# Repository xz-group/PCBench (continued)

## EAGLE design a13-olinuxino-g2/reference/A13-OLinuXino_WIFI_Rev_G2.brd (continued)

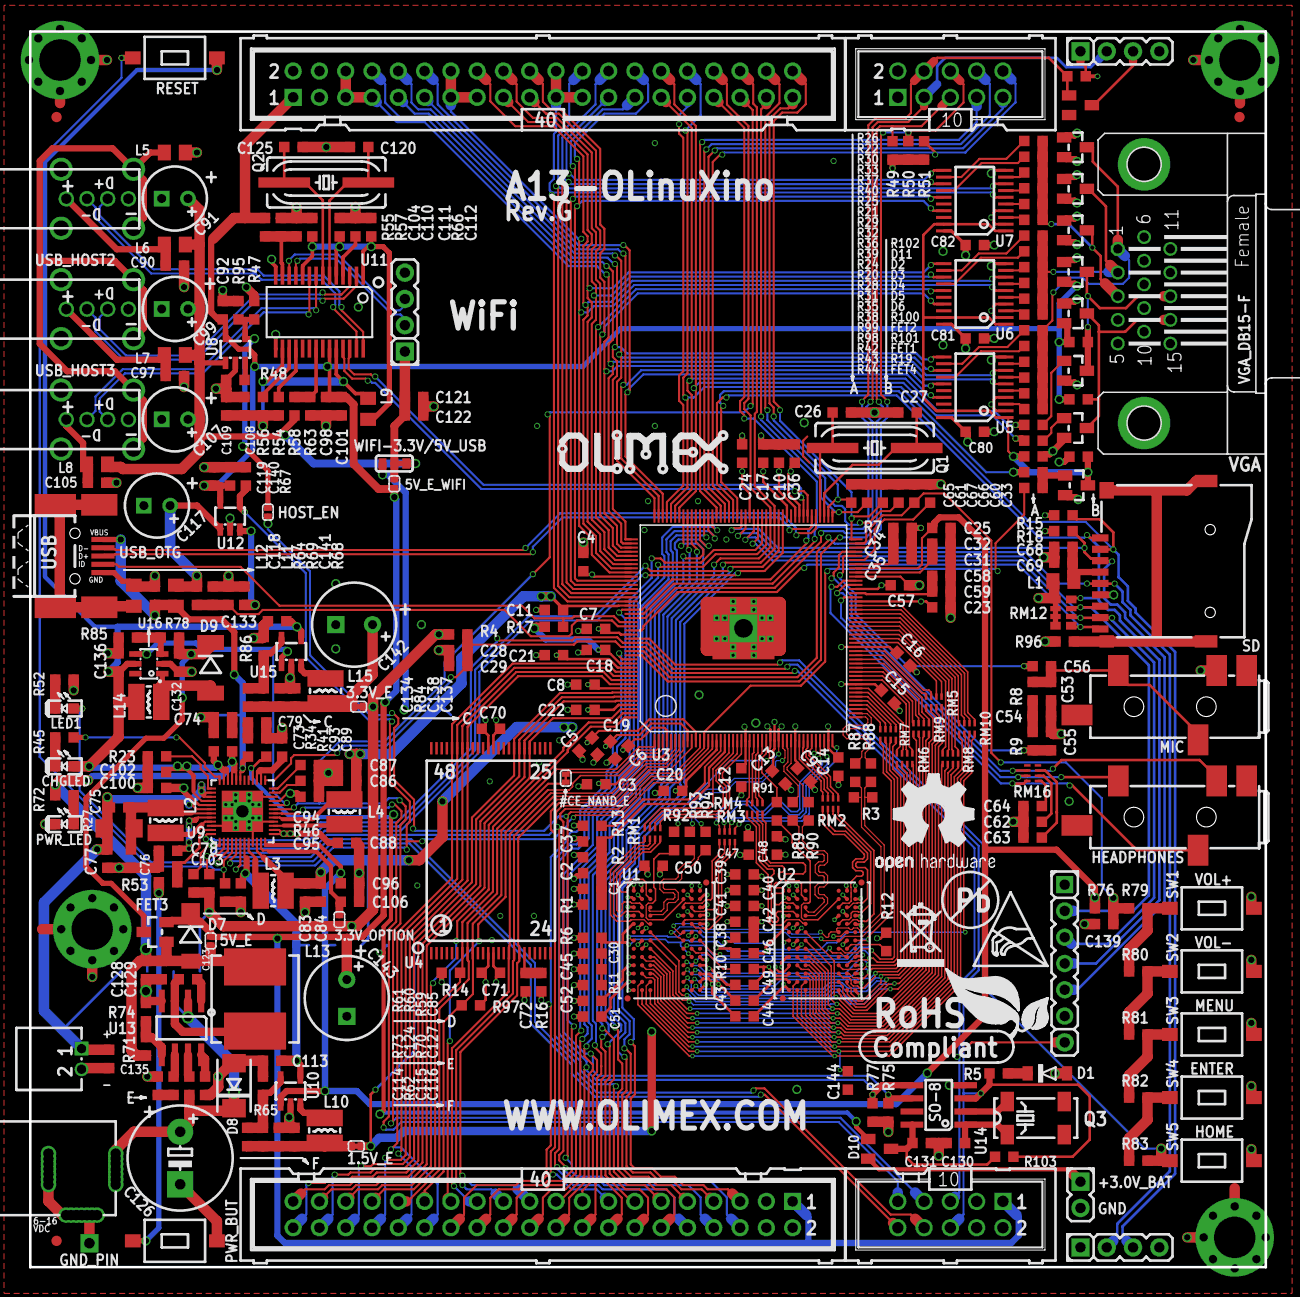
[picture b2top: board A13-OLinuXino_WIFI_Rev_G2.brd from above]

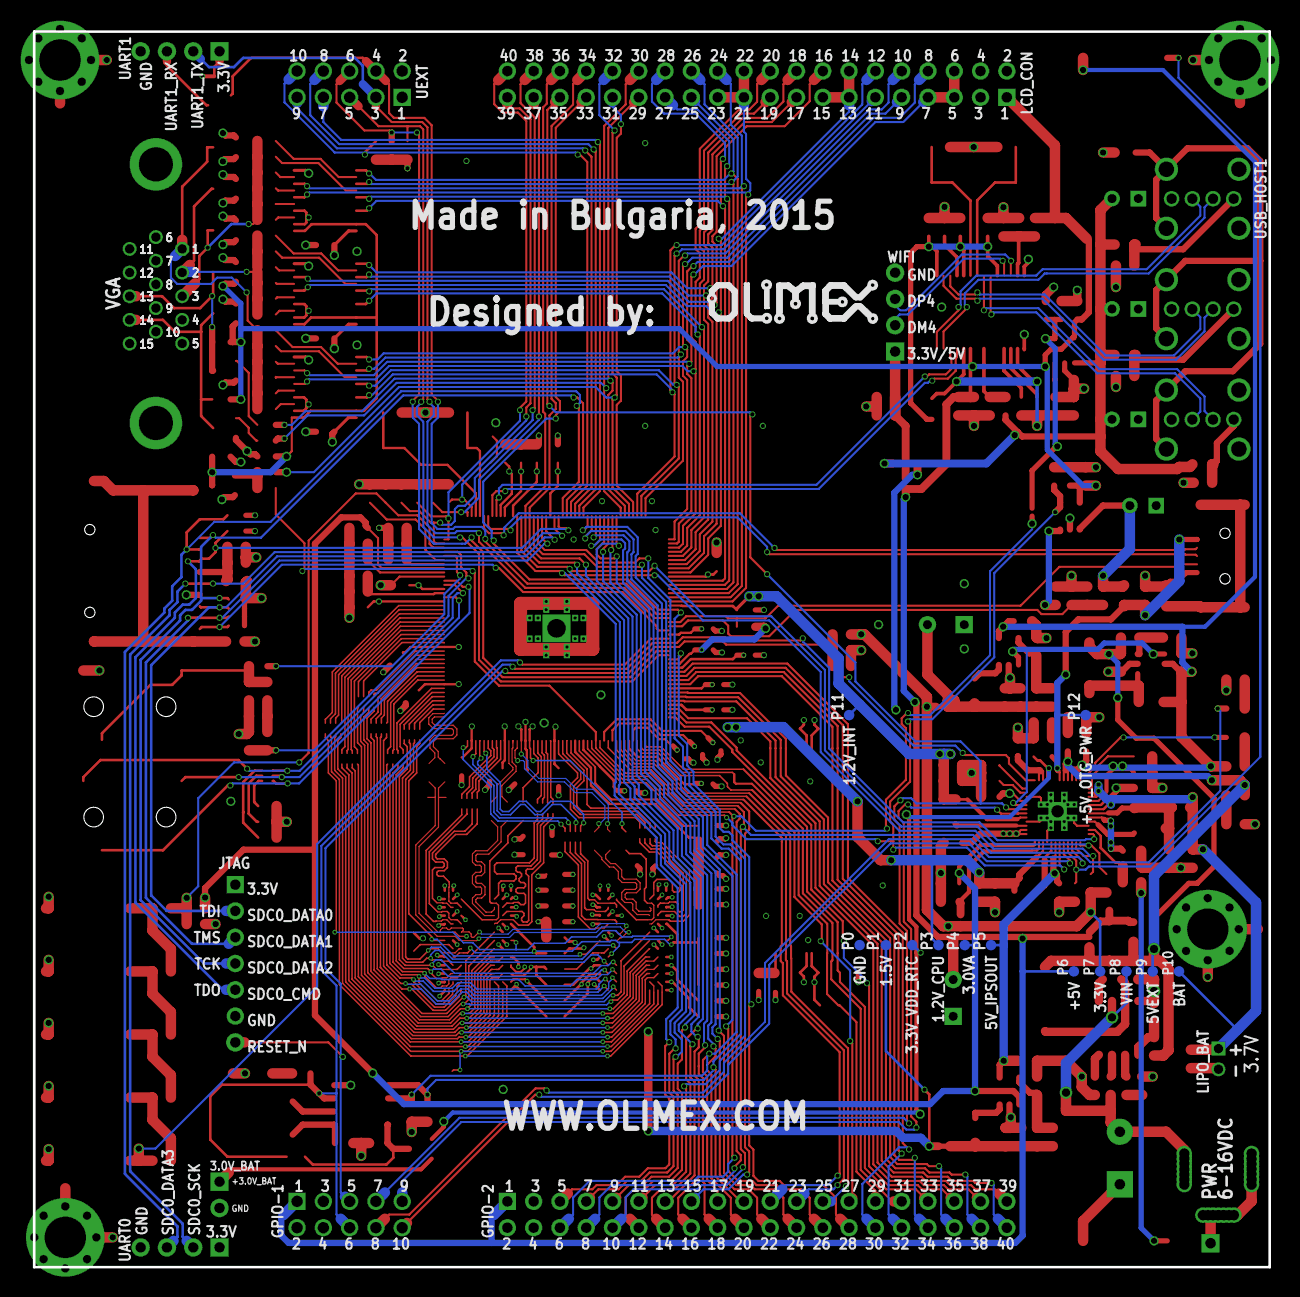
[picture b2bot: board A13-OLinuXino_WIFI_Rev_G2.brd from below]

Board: 4 copper layers, 119.4 x 119.4 mm, 371 parts (14 on the bottom side), 327 nets.

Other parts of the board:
U$5: LOGO-OPENHARDWARE_8X8
U$6, U$8: OLIMEX1_V
U$9: PB
U$10: ESD_SYMBOL
U$11: RECYCLE_BIN1/8
U$12: ROHS

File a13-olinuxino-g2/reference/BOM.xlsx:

Qty | Value | Device | Package | Parts | Description
1 | 0.03R/1% | R-EU_R1206_5MIL_WS | R1206_5MIL_WS | R27 | RESISTOR, European symbol
4 | 1.05k/1% | R-EU_R0603_5MIL_DWS | R0603_5MIL_DWS | R35, R36, R37, R74 | RESISTOR, European symbol
4 | 1.1k/1% | R-EU_R0603_5MIL_DWS | R0603_5MIL_DWS | R19, R85, R100, R101 | RESISTOR, European symbol
3 | 100k/1% | R-EU_R0603_5MIL_DWS | R0603_5MIL_DWS | R69, R76, R84 | RESISTOR, European symbol
57 | 100nF | C-EUC0603_DWS | C0603_DWS | C1, C2, C3, C4, C13, C15, C17, C19, C20, C21, C22, C23, C24, C29, C30, C32, C34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 | CAPACITOR, European symbol
1 | 100pF | C-EUC0603_DWS | C0603_DWS | C144 | CAPACITOR, European symbol
4 | 100uF/16V/LOWESR/105C/6.3x11mm_RM2.5 | CPOL-EUE2.5-6.3 | E2,5-6,3 | C91, C99, C107, C117 | POLARIZED CAPACITOR, European symbol
9 | 10k | R-EU_R0603_5MIL_DWS | R0603_5MIL_DWS | R14, R16, R18, R47, R55, R56, R96, R97, R103 | RESISTOR, European symbol
1 | 10k/1% | R-EU_R0603_5MIL_DWS | R0603_5MIL_DWS | R81 | RESISTOR, European symbol
1 | 10nF | C-EUC0603_DWS | C0603_DWS | C123 | CAPACITOR, European symbol
1 | 10pF | C-EUC0603_DWS | C0603_DWS | C130 | CAPACITOR, European symbol
31 | 10uF/6.3V | C-EUC0603_DWS | C0603_DWS | C6, C7, C8, C10, C11, C14, C16, C31, C35, C54, C55, C58, C73, C74, C76, C77, C7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 | CAPACITOR, European symbol
1 | 10uH/3.15A/20% | LLQH88PN100M38 | 8X8MM_3131 | L13
1 | 11k/1% | R-EU_R0603_5MIL_DWS | R0603_5MIL_DWS | R82 | RESISTOR, European symbol
2 | 13k/1% | R-EU_R0603_5MIL_DWS | R0603_5MIL_DWS | R68, R83 | RESISTOR, European symbol
3 | 17.8k/1% | R-EU_R0603_5MIL_DWS | R0603_5MIL_DWS | R20, R21, R22 | RESISTOR, European symbol
1 | 1N5819(S4SOD-123) | SCHOTKKY7.62SS-1N5819(S4SOD-123) | SOD-123 | D1
1 | 1N5822/SS34/SMA | D-MLL-41 | MELF-MLL41 | D9 | DIODE
1 | 1N5822/SS34/SMA | SCHOTKKY7.62SS2 | MLL-41 | D7
2 | 1R | R-EU_R0603_5MIL_DWS | R0603_5MIL_DWS | R34, R41 | RESISTOR, European symbol
9 | 1nF | C-EUC0603_DWS | C0603_DWS | C60, C61, C65, C66, C67, C84, C87, C103, C139 | CAPACITOR, European symbol
6 | 1uF | C-EUC0603_DWS | C0603_DWS | C28, C33, C75, C89, C94, C104 | CAPACITOR, European symbol
14 | 2.2k | R-EU_R0603_5MIL_DWS | R0603_5MIL_DWS | R8, R9, R45, R49, R50, R52, R53, R59, R60, R61, R72, R73, R75, R77 | RESISTOR, European symbol
3 | 2.2k/1% | R-EU_R0603_5MIL_DWS | R0603_5MIL_DWS | R31, R32, R33 | RESISTOR, European symbol
6 | 2.2uH/1.5A/DCR<0.1R/CD32 | L-CD32 | CD32 | L2, L3, L4, L10, L14, L15
3 | 200k/1% | R-EU_R0603_5MIL_DWS | R0603_5MIL_DWS | R7, R46, R67 | RESISTOR, European symbol
8 | 22R | R-EU_R0603_5MIL_DWS | R0603_5MIL_DWS | R87, R88, R89, R90, R91, R92, R93, R94 | RESISTOR, European symbol
1 | 22k/1% | R-EU_R0603_5MIL_DWS | R0603_5MIL_DWS | R86 | RESISTOR, European symbol
1 | 22pF | C-EUC0603_DWS | C0603_DWS | C114 | CAPACITOR, European symbol
1 | 22uF | C-EUC0603_DWS | C0603_DWS | C140 | CAPACITOR, European symbol
21 | 22uF/6.3V | C-EUC0603_DWS | C0603_DWS | C5, C9, C12, C18, C25, C42, C52, C68, C69, C71, C113, C115, C116, C128, C129, C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 | CAPACITOR, European symbol
4 | 240R/1% | R-EU_R0603_5MIL_DWS | R0603_5MIL_DWS | R10, R12, R13, R23 | RESISTOR, European symbol
4 | 2k/1% | R-EU_R0603_5MIL_DWS | R0603_5MIL_DWS | R1, R2, R6, R11 | RESISTOR, European symbol
1 | 3.3k/1% | R-EU_R0603_5MIL_DWS | R0603_5MIL_DWS | R65 | RESISTOR, European symbol
2 | 3.3nF | C-EUC0603_DWS | C0603_DWS | C53, C124 | CAPACITOR, European symbol
1 | 32768Hz/6pF | MC-306_32.768KHZ/SMD_8038 | MC-306 | Q3
4 | 33pF | C-EUC0603_DWS | C0603_DWS | C26, C27, C120, C125 | CAPACITOR, European symbol
4 | 4.32k/1% | R-EU_R0603_5MIL_DWS | R0603_5MIL_DWS | R28, R29, R30, R102 | RESISTOR, European symbol
2 | 4.99k/1% | R-EU_R0603_5MIL_DWS | R0603_5MIL_DWS | R62, R71 | RESISTOR, European symbol
1 | 470uF/25V/LOWESR/105C | CPOL-EUE5-10.5 | E5-10,5 | C126 | POLARIZED CAPACITOR, European symbol
7 | 47k | R-EU_R0603_5MIL_DWS | R0603_5MIL_DWS | R4, R5, R17, R51, R54, R64, R70 | RESISTOR, European symbol
1 | 47pF | C-EUC0603_DWS | C0603_DWS | C134 | CAPACITOR, European symbol
3 | 51R | R-EU_R0603_5MIL_DWS | R0603_5MIL_DWS | R43, R98, R99 | RESISTOR, European symbol
3 | 549R/1% | R-EU_R0603_5MIL_DWS | R0603_5MIL_DWS | R38, R39, R40 | RESISTOR, European symbol
2 | 6.8k/1% | R-EU_R0603_5MIL_DWS | R0603_5MIL_DWS | R48, R79 | RESISTOR, European symbol
1 | 680R/1% | R-EU_R0603_5MIL_DWS | R0603_5MIL_DWS | R66 | RESISTOR, European symbol
2 | 8.2k/1% | R-EU_R0603_5MIL_DWS | R0603_5MIL_DWS | R78, R80 | RESISTOR, European symbol
3 | 8.66k/1% | R-EU_R0603_5MIL_DWS | R0603_5MIL_DWS | R24, R25, R26 | RESISTOR, European symbol
1 | A13 | Allwinner A13 | TQFP176 | U3
1 | AXP209(QFN48) | AXP209 | QFN48 | U9
2 | BAT54C | DIODE_AC-CA_ | SOT23C | D10, D11 | DUAL DIODE
5 | BAT54S | DIODE_AC-AC_ | SOT23C(BAT54S) | D2, D3, D4, D5, D6 | DUAL DIODE
2 | BH10S | ML10 | ML10-MALE | GPIO-1, UEXT | HARTING
3 | BSS138 | N-MOS+DIODBSS138(SOT23-3) | SOT23 | FET1, FET2, FET4
1 | CL470nH/0805/1.76R/250mA | L-USL0805_5MIL_DWS | L0805_5MIL_DWS | L1 | INDUCTOR, American symbol
1 | DW02R | CON2DW02R | DW02R | LIPO_BAT
1 | FB0805/600R/200mA(201209-601) | L-USL0805_5MIL_DWS | L0805_5MIL_DWS | L12 | INDUCTOR, American symbol
6 | FB0805/600R/2A | L-USL0805_5MIL_DWS | L0805_5MIL_DWS | L5, L6, L7, L8, L9, L11 | INDUCTOR, American symbol
1 | GL850G-HHGXX | GL850G | SSOP28 | U11
2 | HC49/S1 | HC49/S1 | HC49/SMD2_THIN | Q1, Q2 | CRYSTAL
1 | IRLML6402 | P-MOS+DIODIRLML6402 | SOT23 | FET3
2 | K4B2G0846Q-BCKO | H5TQ2G83CFR-H9C | FBGA78 | U1, U2
1 | LED/GREEN/0603 | LED0603DWS | LED-0603 | LED1
1 | LED/RED/0603 | LED0603DWS | LED-0603 | PWR_LED
1 | LED/YELLOW/0603 | LED0603DWS | LED-0603 | CHGLED
1 | MICRO_SD/MMC_CP_NEWTFC-WPAPR-08 | MICRO_SD/MMC_CP_NEWTFC-WPAPR-08 | TFC-WPAPR-08 | SD
2 | 2.54 Pinhead 2x20 | 2.54 Pinhead 2x20 | 2.54 Pinhead 2x20 | GPIO-2, LCD_CON | HARTING
1 | MP1482DS | MP1482 | SOIC8 | U13
1 | PCF8563T/5 | PCF8563 | SO-8 | U14 | Real-time clock/calendar
2 | PJ-W47S-05D2-LF_V2 | AUDIO_JACK_5PINPJ-W47S-05D2-LF_V2 | PJ-W47S-05D2-LF_5PIN_V2 | HEADPHONES, MIC
11 | RA0805_(4X0402)_22R | R_MATRIX_4E_25X625 | R_MATRIX_4_0402_25X625 | RM1, RM2, RM3, RM4, RM5, RM6, RM7, RM8, RM9, RM10, RM16
1 | RA1206_(4X0603)_4B8_100K | R_MATRIX_4E | R_MATRIX_4 | RM12
1 | SMBJ16A | SMBJ16A | DO214AA | D8
3 | SN74ALVC244 | 74ALVC244 | PW | U5, U6, U7
2 | SY6280 | SY6280 | SOT23-5 | U8, U12
1 | SY7208(SOT23-6) | SY7208 | SOT23-6 | U16
2 | SY8008C(AA)C | SY8008 | SOT23-5 | U10, U15
7 | T1107A(6x3.8x2.5mm) | SW-TAKT6 | SW-TAKT_6X3.5_SMD | PWR_BUT, RESET, SW1, SW2, SW3, SW4, SW5
1 | USB-OTG | MINI_USB9 | USB_MINI_9PIN | USB_OTG
3 | USB_A_VERTICAL | USB_SHIELDUSB_A_VERTICAL | USB_A_VERTICAL_PTH | USB_HOST1, USB_HOST2, USB_HOST3
1 | VGA15 | DB1522 | DB15-F_22MM | VGA_DB15-F
1 | YDJ-1136 | PWR-JAKPWR_JACK_UNI_MILLING | PWR_JACK_UNI_MILLING | PWR

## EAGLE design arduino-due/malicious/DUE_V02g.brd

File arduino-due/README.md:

# Getting Started with the Arduino-Due Benchmark

## Introduction
This tutorial includes step-by-step information about how to get started with the `arduino-due` benchmark, including both setting up the boards and demonstrating the attacks.

For this benchmark, there are two versions of boards (as shown below): the  `malicious` version and the `reference` version. The `reference` version uses the exact same schematic design of the original [Arduino Due board](https://store.arduino.cc/usa/due). 
Note that we slightly modify the layout of the original design to ease inserting the Trojans and implementing the attacks. The `malicious` version is the same as the `reference` version (both schematic and layout) except the inserted malicious circuit, which means once the malicious circuits and related routings are removed, the `malicious` version board will be completely the same as the `reference` version board.

In this benchmark we implement three malicious attacks (as shown above):
1. A malicious MOSFET is connected to the UART transmitter to leak information through LED (subfigure c);
2. The maliciously programmed ATtiny microcontroller monitors the UART and generates Flash erase signal when triggered (subfigure d); 
3. Two XOR logic chips output a signal to reset the board once triggered (subfigure e).

## Initialize the boards
### Install the firmware of the Arduino Due programming port
#### Use the Atmel programmer to install the firmware:
1. Follow the instruction of https://www.arduino.cc/en/Hacking/DFUProgramming8U2

2. For the firmware files, the `hex` files can be found in
https://github.com/arduino/ArduinoCore-sam/tree/master/firmwares/atmega16u2

3. After programming the flash, you will see the programming port of the Arduino Due board in your Device manager.

### Test the functionality of the boards
1. Install the Arduino SAM Boards (32-bits ARM Cortex M3) from the tools->board->boards manager.
#### Program through the Programming Port
1. Connect the Programming Port.
2. Upload and Run the `Blink` example.

#### Program through the Native USB Port

1. Connect the native USB port.
2. Program directly using the native USB port, upload and Run the `Blink` example.

## Demonstrate the attacks
### 1. Malicious MOSFET
**Goal:**<br> A malicious MOSFET is connected to the UART transmit pin to leak information through LED.

**Configuration:**<br> In this demonstration, the datapath is as follows:
User input into the reference board's Serial Monitor is sent directly to the Serial1 port on the victim board. This Serial1 port (on the victim board) is directly connected to the LED that is used to leak the data. Once the victim board receives data from the reference board, it mirrors the characters back over the same Serial1 port to be leaked through the LED. The data is also mirrored to the SerialUSB port which will display on the victim board's Serial Monitor if connected.

**Demonstration:**<br>

1. Connect Pins

| Reference Board | <------------> | Victim Board |
| ----------- | ----------- | ----------- |
| Serial1 TX (18) | <------------> | Serial1 RX (19) |
| Serial1 RX (19) | <------------> | Serial1 TX (18) |
| GND | <------------> | GND |

2. Upload Source Code

* Attach the victim board via USB and upload the following [source code](attacks/malicious_MOSFET/victim_board_src/victim_board_src.ino)
* Attach the reference board via USB and upload the following [source code](attacks/malicious_MOSFET/reference_board_src/reference_board_src.ino)

3. Testing

* Connect the reference board via USB
* Open the Serial Monitor (this is accessed by clicking the plus button in the top right corner on the Arduino IDE)
* Click the hardware reset button (located next to the USB port) on the reference board
* Wait 5 seconds for the board to initialize until you see an information printout
* Try entering various characters into the Serial Monitor
* Take note of the LED blinking on the victim board whenever characters are sent via the reference board
* To confirm that characters are being sent, connect the reference board via USB and open another Serial Monitor to track the mirrored characters being sent from the reference board

**Vulnerability:**<br> The flashing of the LED corresponds to the 1's and 0's of the ASCII being transmitted through UART. This data could be sensed and decoded by another system to monitor sensitive UART data packets.

### 2. Malicious ATtiny
**Goal:**<br> A maliciously programmed ATtiny microcontroller monitors the UART and generates a Flash erase signal when triggered.

**Generalized Configuration:**<br> In this demonstration, the datapath is as follows:
User input into the reference board's Serial Monitor is sent directly to the Serial2 port on the victim board. This Serial2 port (on the victim board) is directly monitored by the malicious ATtiny. Once the trigger word is inputted by the user and subsequently read by the ATtiny, the ATtiny triggers a master reset of the victim board's flash memory. Throughout this process, the victim board's LED will continuously blink to show that it is still functional and has not yet been attacked. Once it is attacked, the LED will stop blinking and the board will have to be re-flashed before it can perform another test.

**Technical Configuration:**<br>
* The ATtiny102 constantly monitors the victim board's UART RX pin at 4800 baud
    * This connection configuration is undetectable by the victim board itself or any reference boards
* A reference board is used to connect to the Serial 2 UART Port of the victim board (TX-16 RX-17)
    * The reference board can trigger the ATtiny102 to erase the flash of the victim board by sending the command "ATTACK"
* A 6-character buffer array is maintined on the ATtiny102 to keep track of incoming UART characters
    * Each time a new character is read, it is placed at the end of the array
    * Subsequently, all remaining characters are shifted one index to the left in the array
    * This process discards the oldest (leftmost) character
* Once the buffer array contains the string "ATTACK" the ERASE sequence is triggered:
    * The ATtiny102 pulls the ERASE pin of the victim board LOW for 2 seconds to erase the FLASH
    * At this point, the victim board is in a paralyzed state and the ATtiny102 resumes normal listening operation

**Demonstration:**
1. Connect Pins

| Reference Board | <------------> | Victim Board |
| ----------- | ----------- | ----------- |
| Serial2 TX (16) | <------------> | Serial1 RX (17) |
| Serial1 RX (17) | <------------> | Serial1 TX (16) |
| GND | <------------> | GND |

2. Upload Source Code

* Attach the victim board via USB and upload the following [source code](attacks/malicious_ATtiny/victim_board_src/victim_board_src.ino)
* Attach the reference board via USB and upload the following [source code](attacks/malicious_ATtiny/reference_board_src/reference_board_src.ino)
* If the ATtiny needs to be flashed, use Atmel/Microchip Studio to upload the following [source code](attacks/malicious_ATtiny/ATtiny_src)

3. Testing

* Connect the reference board via USB
* Open the Serial Monitor (this is accessed by clicking the plus button in the top right corner on the Arduino IDE)
* Click the hardware reset button (located next to the USB port) on the reference board
* Wait 5 seconds for the board to initialize until you see an information printout
* Try entering various characters (not the trigger word) into the Serial Monitor
* Take note of the LED blinking on the victim board which signifies that it has not yet been attacked
* Enter the trigger word into the Serial Monitor
* Confirm that the attack was successful be ensuring that the victim board's LED stopped blinking

**Vulnerability:**<br> The ATtiny can erase the Flash of the victim board, rendering it useless, if the trigger command is sent to the victim board over UART.

### 3. Malicious XORs
**Goal:**<br> Two XOR logic chips output a signal to reset the victim board's Flash once triggered.

**Generalized Configuration:**<br> In this demonstration, the datapath is as follows:
User input into the reference board's Serial Monitor is monitored internally by the reference board. Once the trigger word is inputted by the user, a sequence of code executes that triggers a flash reset on the victim board. This is accomplished by setting pins 44, 45, and 46 on the victim board to a specific sequence of logic levels that trigger the flash reset. Throughout this process, the victim board's LED will continuously blink to show that it is still functional and has not yet been attacked. Once it is attacked, the LED will stop blinking and the board will have to be re-flashed before it can perform another test.

**Technical Configuration:**<br>
* The XOR chips have pins 44, 45, 46 from the victim board as inputs. In the default state, these pins are logical level HIGH so as to not trigger the Flash reset.
* The following truth table represents the various logic level inputs to the victim board and what output they trigger

| Pin 44      | Pin 45      | Pin 46      | Flash Reset |
| ----------- | ----------- | ----------- | -----------  |
|0|0|0|NO|
|0|0|1|<mark>YES<mark>|
|0|1|0|<mark>YES<mark>|
|0|1|1|NO|
|1|0|0|<mark>YES<mark>|
|1|0|1|NO|
|1|1|0|NO|
|1|1|1|<mark>YES<mark>|

**Demonstration:**
1. Connect Pins

| Reference Board | <------------> | Victim Board |
| ----------- | ----------- | ----------- |
| D10 | <------------> | D44 |
| D11 | <------------> | D45 |
| D12 | <------------> | D46 |
| GND | <------------> | GND |

2. Upload Source Code

* Attach the victim board via USB and upload the following [source code](attacks/malicious_ATtiny/victim_board_src/victim_board_src.ino)
* Attach the reference board via USB and upload the following [source code](attacks/malicious_ATtiny/reference_board_src/reference_board_src.ino)

3. Testing

* Connect the reference board via USB
* Open the Serial Monitor (this is accessed by clicking the plus button in the top right corner on the Arduino IDE)
* Click the hardware reset button (located next to the USB port) on the reference board
* Wait 5 seconds for the board to initialize until you see an information printout
* Try entering various characters (not the trigger word) into the Serial Monitor
* Take note of the LED blinking on the victim board which signifies that it has not yet been attacked
* Enter the trigger word into the Serial Monitor
* Confirm that the attack was successful be ensuring that the victim board's LED stopped blinking

**Vulnerability:**<br> An external board can change the state of these input pins which would trigger a Flash reset of the victim board, rendering is useless.

## Developer Notes
* For an 8MHz internal clock on the ATtiny102, the prescaler sets the clock in the code to 1MHz
    * 1 MHz is not considered fast enough to communicated over UART at 9600 baud becuase data becomes corrupted
    * 4800 is the maximum clean baud rate for this internal clock
* ATtiny102 TX trace should be removed in final design
* Use other, non-programming pin, for the resetting functionality on the ATtiny102 (recommend PB1/Pin 5)
* The programming port on the test boards does not work due to a an error in the original Arduino Due design documentation

## References
1. Pinout of the Arduino Due Board: https://content.arduino.cc/assets/Pinout-Due_latest.pdf

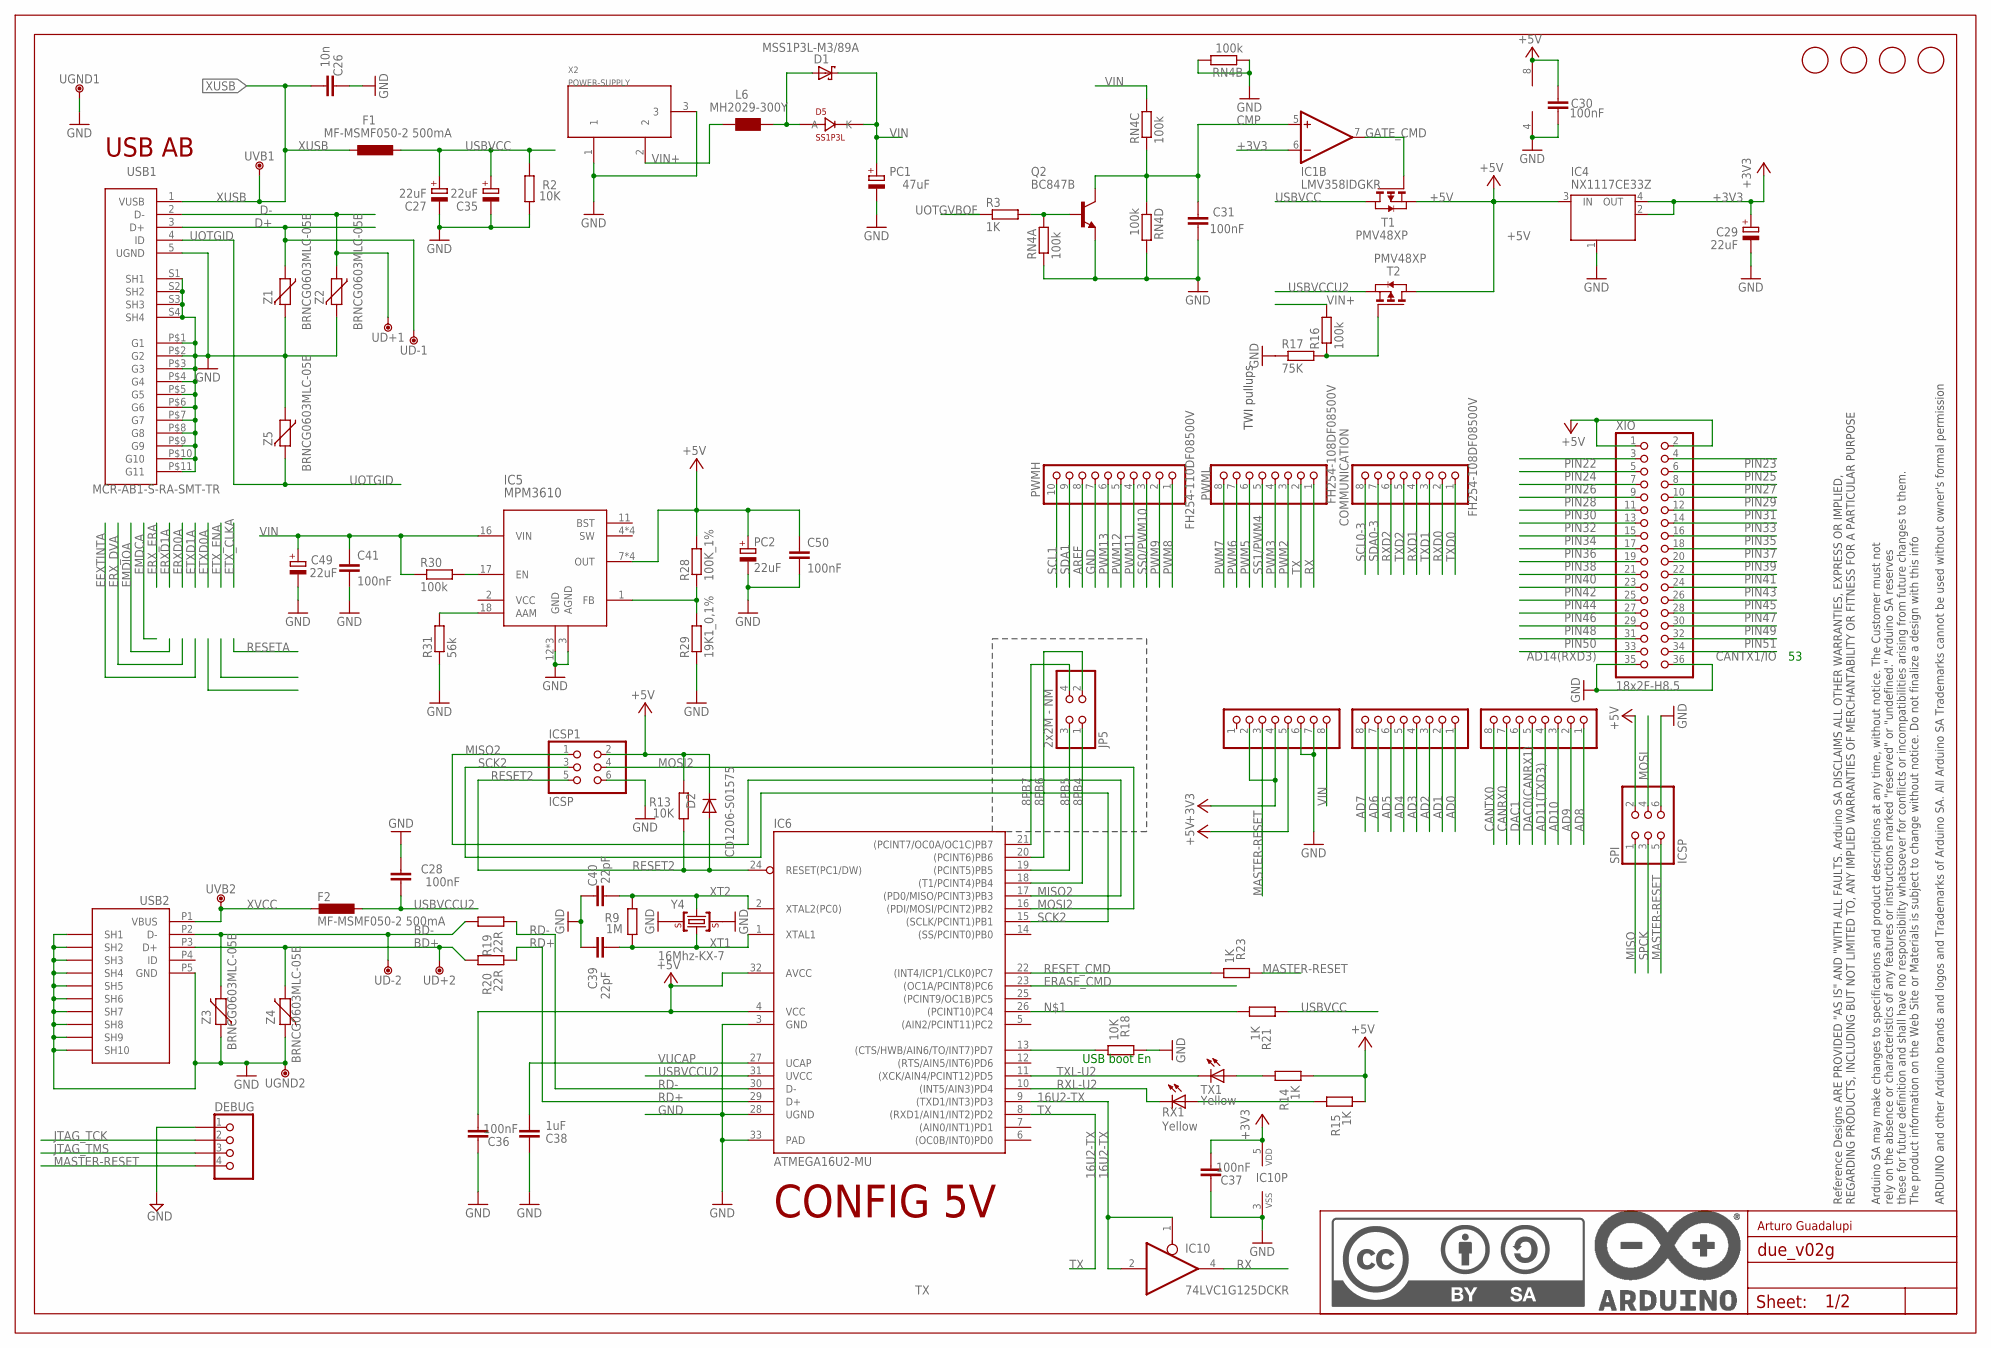
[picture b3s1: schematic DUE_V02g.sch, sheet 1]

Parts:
ADCH: FH254-108DF08500V; 1X08
ADCL: FH254-108DF08500V; 1X08
C26: 10n; C0402
C27, C29, C35, C49: 22uF; SMC_B
C28, C30, C31, C36, C37: 100nF; C0402
C38: 1uF; C0402
C39, C40: 22pF; C0402
C41, C50: 100nF; C0603-ROUND
COMMUNICATION: FH254-108DF08500V; 1X08
D1: MSS1P3L-M3/89A; MICROSMP
D2: CD1206-S01575; MINIMELF
D5: SS1P3L; DO220AAL
DEBUG: 0644_4X1VP.2,54H11,8; PH1X4-THT
F1, F2: MF-MSMF050-2 500mA; L1812
FID1, FID2, FID3, FID4: FIDUCIALMOUNT; FIDUCIA-MOUNT
IC1: LMV358IDGKR; MSOP08
IC4: NX1117CE33Z; SOT223
IC5: MPM3610; QFN-20
IC6: ATMEGA16U2-MU; MLF32
IC10: 74LVC1G125DCKR; SC70-5
ICSP1: ICSP; 2X03
JP5: 2x2M - NM; 2X02
L6: MH2029-300Y; 0805
PC1: 47uF; PANASONIC_D
PC2: 22uF; SMC_B
POWER: FH254-108DF08500V; 1X08
PWMH: FH254-110DF08500V; 1X10
PWML: FH254-108DF08500V; 1X08
Q2: BC847B; SOT23
R2, R13, R18: 10K; R0402
R3, R14, R15, R21, R23: 1K; R0402
R9: 1M; R0402
R16: 100k; R0402
R17: 75K; R0603-ROUND
R19, R20: 22R; R0402
R28: 100K_1%; R0603-ROUND
R29: 19K1_0,1%; R0603-ROUND
R30: 100k; R0603-ROUND
R31: 56k; R0603-ROUND
RN4: 100k; CAY16
RX1: Yellow; CHIPLED_0805
SPI: ICSP; 2X03
T1, T2: PMV48XP; SOT-23
TX1: Yellow; CHIPLED_0805
U$1: DNP; FRAME
UD+1, UD+2: DNP; TP-1.00MM
UD-1, UD-2: DNP; TP-1.00MM
UGND1, UGND2: DNP; TP-1.00MM
USB1: MCR-AB1-S-RA-SMT-TR; MCR-AB1-S-RA-SMT
USB2: MCR-B-S-RA-SMT-CS1TR; CON2_USB_MICRO_B_AT
UVB1, UVB2: DNP; TP-1.00MM
X2: POWER-SUPPLY; POWERSUPPLY_DC-21MM
XIO: 18x2F-H8.5; 2X18
Y4: 16Mhz-KX-7; CRYSTAL-3.2-2.5
Z1, Z2, Z3, Z4, Z5: BRNCG0603MLC-05E; CT/CN0603

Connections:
8PB4: IC6.18 ((T1/PCINT4)PB4), JP5.1
8PB5: IC6.19 ((PCINT5)PB5), JP5.3
8PB6: IC6.20 ((PCINT6)PB6), JP5.2
8PB7: IC6.21 ((PCINT7/OC0A/OC1C)PB7), JP5.4
16U2-TX: IC6.9 ((TXD1/INT3)PD3), IC10.1 (OE), IC10.2 (I)
+3V3: C29.+, C37.1, IC1.6 (-IN), IC4.2 (OUT), IC4.4 (OUT), IC10.5 (VDD), POWER.2, POWER.4; also elsewhere on the board
+5V: C30.2, C36.1, C50.1, D2.C, IC1.8 (V+), IC4.3 (IN), IC5.7 (OUT), IC5.8 (OUT), IC5.9 (OUT), IC5.20 (OUT), IC6.4 (VCC), IC6.32 (AVCC), ICSP1.2, PC2.+, POWER.5, R13.2, R14.1, R15.1, R28.2, SPI.2, T1.2 (S), T2.1 (D), XIO.1, XIO.2
AD0: ADCL.1; also elsewhere on the board
AD1: ADCL.2; also elsewhere on the board
AD2: ADCL.3; also elsewhere on the board
AD3: ADCL.4; also elsewhere on the board
AD4: ADCL.5; also elsewhere on the board
AD5: ADCL.6; also elsewhere on the board
AD6: ADCL.7; also elsewhere on the board
AD7: ADCL.8; also elsewhere on the board
AD8: ADCH.1; also elsewhere on the board
AD9: ADCH.2; also elsewhere on the board
AD10: ADCH.3; also elsewhere on the board
AD11(TXD3): ADCH.4; also elsewhere on the board
AD14(RXD3): XIO.33; also elsewhere on the board
AREF: PWMH.8; also elsewhere on the board
BD+: R20.2, UD+2.X, USB2.P3 (D+), Z4.2
BD-: R19.2, UD-2.X, USB2.P2 (D-), Z3.2
CANRX0: ADCH.7; also elsewhere on the board
CANTX0: ADCH.8; also elsewhere on the board
CANTX1/IO: XIO.34; also elsewhere on the board
CMP: C31.2, IC1.5 (+IN), Q2.3 (C), RN4.3 (1), RN4.4 (1)
D+: UD-1.X, USB1.3 (D+), Z1.1; also elsewhere on the board
D-: UD+1.X, USB1.2 (D-), Z2.1; also elsewhere on the board
DAC0(CANRX1): ADCH.5; also elsewhere on the board
DAC1: ADCH.6; also elsewhere on the board
DTR: IC6.13 ((CTS/HWB/AIN6/TO/INT7)PD7), R18.1
ERASE_CMD: IC6.23 ((OC1A/PCINT8)PC6); also elsewhere on the board
GATE_CMD: IC1.7 (OUT), T1.3 (G)
GND: C26.2, C27.-, C28.2, C29.-, C30.1, C31.1, C35.-, C36.2, C37.2, C38.2, C39.2, C40.2, C41.2, C49.-, C50.2, DEBUG.1, IC1.4 (V-), IC4.1 (GND/ADJ), IC5.3 (AGND), IC5.12 (GND), IC5.13 (GND), IC5.14 (GND), IC6.3 (GND), IC6.28 (UGND), IC6.33 (PAD), IC10.3 (VSS), ICSP1.6, PC1.-, PC2.-, POWER.6, POWER.7, PWMH.7, Q2.2 (E), R2.1, R17.1, R18.2, R29.1, R31.1, RN4.1, RN4.2 (1), RN4.5 (2), RN4.7 (2), SPI.6, UGND1.X, UGND2.X, USB1.5 (UGND), USB1.P$1 (G1), USB1.P$2 (G2), USB1.P$3 (G3), USB1.P$4 (G4), USB1.P$5 (G5), USB1.P$6 (G6), USB1.P$7 (G7), USB1.P$8 (G8), USB1.P$9 (G9), USB1.P$10 (G10), USB1.P$11 (G11), USB1.S1 (SH1), USB1.S2 (SH2), USB1.S3 (SH3), USB1.S4 (SH4), USB2.P5 (GND), USB2.P$1 (SH7), USB2.P$2 (SH8), USB2.P$3 (SH9), USB2.P$4 (SH10), USB2.P$5 (SH7), USB2.P$6 (SH8), USB2.P$7 (SH9), USB2.P$8 (SH10), USB2.S1 (SH1), USB2.S2 (SH2), USB2.S3 (SH3), USB2.S4 (SH4), USB2.S5 (SH5), USB2.S6 (SH6), X2.1, X2.3, XIO.35, XIO.36, Y4.2 (GND), Y4.4 (GND), Z1.2, Z2.2, Z3.1, Z4.1, Z5.1; also elsewhere on the board
JTAG_TCK: DEBUG.2; also elsewhere on the board
JTAG_TMS: DEBUG.3; also elsewhere on the board
MASTER-RESET: DEBUG.4, POWER.3, R23.2, SPI.5; also elsewhere on the board
MISO: SPI.1; also elsewhere on the board
MISO2: IC6.17 ((PD0/MISO/PCINT3)PB3), ICSP1.1
MOSI: SPI.4; also elsewhere on the board
MOSI2: IC6.16 ((PDI/MOSI/PCINT2)PB2), ICSP1.4
unnamed: IC6.26 ((PCINT10)PC4), R21.1
unnamed: R15.2, RX1.A
unnamed: Q2.1 (B), R3.2, RN4.8 (2)
unnamed: D1.A, D5.P$2 (A), L6.1
unnamed: R14.2, TX1.A
unnamed: R16.1, R17.2, T2.3 (G)
unnamed: IC5.1 (FB), R28.1, R29.2
unnamed: IC5.17 (EN), R30.2
unnamed: IC5.18 (AAM), R31.2
PIN22: XIO.3; also elsewhere on the board
PIN23: XIO.4; also elsewhere on the board
PIN24: XIO.5; also elsewhere on the board
PIN25: XIO.6; also elsewhere on the board
PIN26: XIO.7; also elsewhere on the board
PIN27: XIO.8; also elsewhere on the board
PIN28: XIO.9; also elsewhere on the board
PIN29: XIO.10; also elsewhere on the board
PIN30: XIO.11; also elsewhere on the board
PIN31: XIO.12; also elsewhere on the board
PIN32: XIO.13; also elsewhere on the board
PIN33: XIO.14; also elsewhere on the board
PIN34: XIO.15; also elsewhere on the board
PIN35: XIO.16; also elsewhere on the board
PIN36: XIO.17; also elsewhere on the board
PIN37: XIO.18; also elsewhere on the board
PIN38: XIO.19; also elsewhere on the board
PIN39: XIO.20; also elsewhere on the board
PIN40: XIO.21; also elsewhere on the board
PIN41: XIO.22; also elsewhere on the board
PIN42: XIO.23; also elsewhere on the board
PIN43: XIO.24; also elsewhere on the board
PIN44: XIO.25; also elsewhere on the board
PIN45: XIO.26; also elsewhere on the board
PIN46: XIO.27; also elsewhere on the board
PIN47: XIO.28; also elsewhere on the board
PIN48: XIO.29; also elsewhere on the board
PIN49: XIO.30; also elsewhere on the board
PIN50: XIO.31; also elsewhere on the board
PIN51: XIO.32; also elsewhere on the board
PWM2: PWML.3; also elsewhere on the board
PWM3: PWML.4; also elsewhere on the board
PWM5: PWML.6; also elsewhere on the board
PWM6: PWML.7; also elsewhere on the board
PWM7: PWML.8; also elsewhere on the board
PWM8: PWMH.1; also elsewhere on the board
PWM9: PWMH.2; also elsewhere on the board
PWM11: PWMH.4; also elsewhere on the board
PWM12: PWMH.5; also elsewhere on the board
PWM13: PWMH.6; also elsewhere on the board
RD+: IC6.29 (D+), R20.1
RD-: IC6.30 (D-), R19.1
RESET2: D2.A, IC6.24 (RESET(PC1/DW)), ICSP1.5, R13.1
RESET_CMD: IC6.22 ((INT4/ICP1/CLK0)PC7), R23.1
RX: IC10.4 (O), PWML.1; also elsewhere on the board
RXD0: COMMUNICATION.2; also elsewhere on the board
RXD1: COMMUNICATION.4; also elsewhere on the board
RXD2: COMMUNICATION.6; also elsewhere on the board
RXL-U2: IC6.10 ((INT5/AIN3)PD4), RX1.C
SCK2: IC6.15 ((SCLK/PCINT1)PB1), ICSP1.3
SCL0-3: COMMUNICATION.8; also elsewhere on the board
SCL1: PWMH.10; also elsewhere on the board
SDA0-3: COMMUNICATION.7; also elsewhere on the board
SDA1: PWMH.9; also elsewhere on the board
SPCK: SPI.3; also elsewhere on the board
SS0/PWM10: PWMH.3; also elsewhere on the board
SS1/PWM4: PWML.5; also elsewhere on the board
TX: IC6.8 ((RXD1/AIN1/INT2)PD2), PWML.2; also elsewhere on the board
TXD0: COMMUNICATION.1; also elsewhere on the board
TXD1: COMMUNICATION.3; also elsewhere on the board
TXD2: COMMUNICATION.5; also elsewhere on the board
TXL-U2: IC6.11 ((XCK/AIN4/PCINT12)PD5), TX1.C
UOTGID: USB1.4 (ID), Z5.2; also elsewhere on the board
UOTGVBOF: R3.1; also elsewhere on the board
USBVCC: C27.+, C35.+, F1.1, R2.2, R21.2, T1.1 (D)
USBVCCU2: C28.1, F2.1, IC6.31 (UVCC), T2.2 (S)
VIN: C41.1, C49.+, D1.K (C), D5.P$1 (K), IC5.16 (VIN), PC1.+, POWER.8, R30.1, RN4.6 (2)
VIN+: L6.2, R16.2, X2.2
VUCAP: C38.1, IC6.27 (UCAP)
XT1: C39.1, IC6.1 (XTAL1), R9.1, Y4.1 (C1)
XT2: C40.1, IC6.2 (XTAL2(PC0)), R9.2, Y4.3 (C2)
XUSB: C26.1, F1.2, USB1.1 (VUSB), UVB1.X; also elsewhere on the board
XVCC: F2.2, USB2.P1 (VBUS), UVB2.X

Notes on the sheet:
TWI pullups
USB AB
USB boot En
CONFIG 5V
Arturo Guadalupi
